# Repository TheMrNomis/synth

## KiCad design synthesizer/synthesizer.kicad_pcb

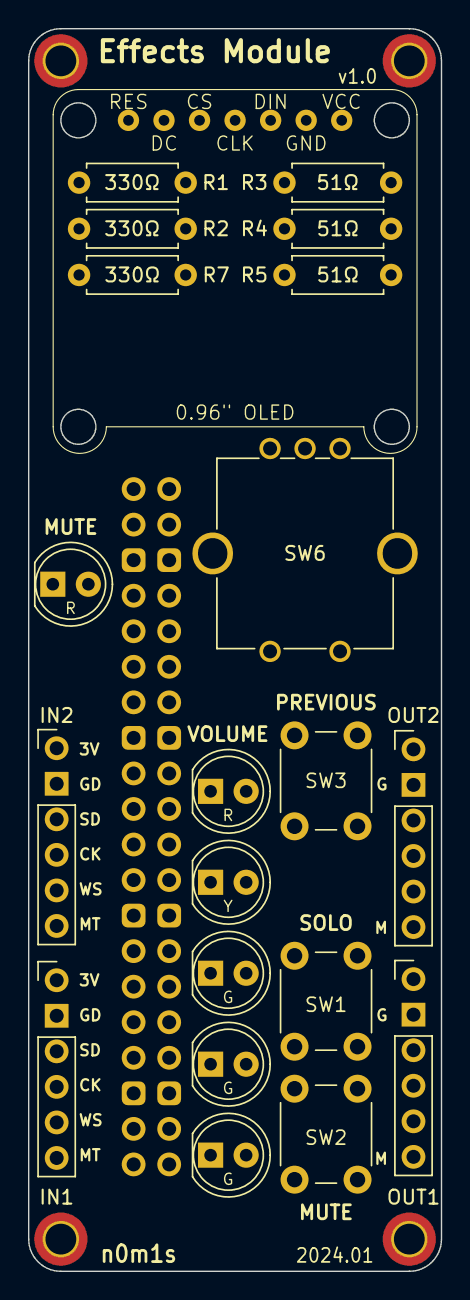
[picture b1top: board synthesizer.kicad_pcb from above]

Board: 2 copper layers, 29.5 x 88.8 mm, 26 parts (1 on the bottom side), 26 nets, no tracks yet.

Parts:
D2: RED; LED_D5.0mm
H1, H2, H3, H4: MountingHole_Pad; MountingHole_2.2mm_M2_DIN965_Pad_TopBottom
IN1, IN2: PannelConnector
OUT1, OUT2: PannelConnector
R1, R2, R7: 330Ω; R_Axial_DIN0207_L6.3mm_D2.5mm_P7.62mm_Horizontal
R3, R4, R5: 51Ω; R_Axial_DIN0207_L6.3mm_D2.5mm_P7.62mm_Horizontal
S1: 0.96inOLED
SW1: SW_SOLO; SW_PUSH_6mm_H5mm
SW2: SW_MUTE; SW_PUSH_6mm_H5mm
SW3: SW_PREV; SW_PUSH_6mm_H5mm
SW6: RotaryEncoder_Switch; RotaryEncoder_Bourns_Vertical_PEC12R-3xxxF-Sxxxx
U1: RaspberryPi_Pico; RPi_connector
VU1: RED; LED_D5.0mm
VU2: YELLOW; LED_D5.0mm
VU3, VU4, VU5: GREEN; LED_D5.0mm

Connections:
+3.3V: IN1.1 (VIN), IN2.1 (VIN), OUT1.1 (VIN), OUT2.1 (VIN), S1.7 (VCC), U1.36 (3V3)
/I2S_IN1_SCK: IN1.4 (SCK), U1.14 (GPIO10)
/I2S_IN1_SD: IN1.3 (SD), U1.12 (GPIO9)
/I2S_IN1_WS: IN1.5 (WS), U1.15 (GPIO11)
/I2S_IN2_SCK: IN2.4 (SCK), U1.10 (GPIO7)
/I2S_IN2_SD: IN2.3 (SD), U1.9 (GPIO6)
/I2S_IN2_WS: IN2.5 (WS), U1.11 (GPIO8)
/I2S_OUT_SCK: OUT1.4 (SCK), OUT2.4 (SCK), U1.19 (GPIO14)
/I2S_OUT_SD: OUT1.3 (SD), OUT2.3 (SD), U1.17 (GPIO13)
/I2S_OUT_WS: OUT1.5 (WS), OUT2.5 (WS), U1.20 (GPIO15)
/MUTE_BTN: SW2.2, U1.16 (GPIO12)
/MUTE_LED: D2.2 (A), U1.1 (GPIO0)
/MUTE_SIG: IN1.6 (MUTE), IN2.6 (MUTE), OUT1.6 (MUTE), OUT2.6 (MUTE), U1.29 (GPIO22)
/R7D2: D2.1 (K), R7.2
/SOLO_BTN: SW1.2, U1.27 (GPIO21)
/VU_GREEN1: U1.24 (GPIO18), VU3.2 (A)
/VU_GREEN2: U1.22 (GPIO17), VU4.2 (A)
/VU_GREEN3: U1.21 (GPIO16), VU5.2 (A)
/VU_R1: R1.2, VU1.1 (K)
/VU_R2: R2.2, VU2.1 (K)
/VU_R3: R3.2, VU3.1 (K)
/VU_R4: R4.2, VU4.1 (K)
/VU_R5: R5.2, VU5.1 (K)
/VU_RED: U1.26 (GPIO20), VU1.2 (A)
/VU_YELLOW: U1.25 (GPIO19), VU2.2 (A)
GND: H1.1, H2.1, H3.1, H4.1, IN1.2 (GND), IN2.2 (GND), OUT1.2 (GND), OUT2.2 (GND), R1.1, R2.1, R3.1, R4.1, R5.1, R7.1, S1.6 (GND), SW1.1, SW2.1, SW3.1, SW6.S2, U1.3 (GND), U1.8 (GND), U1.13 (GND), U1.18 (GND), U1.23 (GND), U1.28 (GND), U1.33 (AGND), U1.38 (GND)

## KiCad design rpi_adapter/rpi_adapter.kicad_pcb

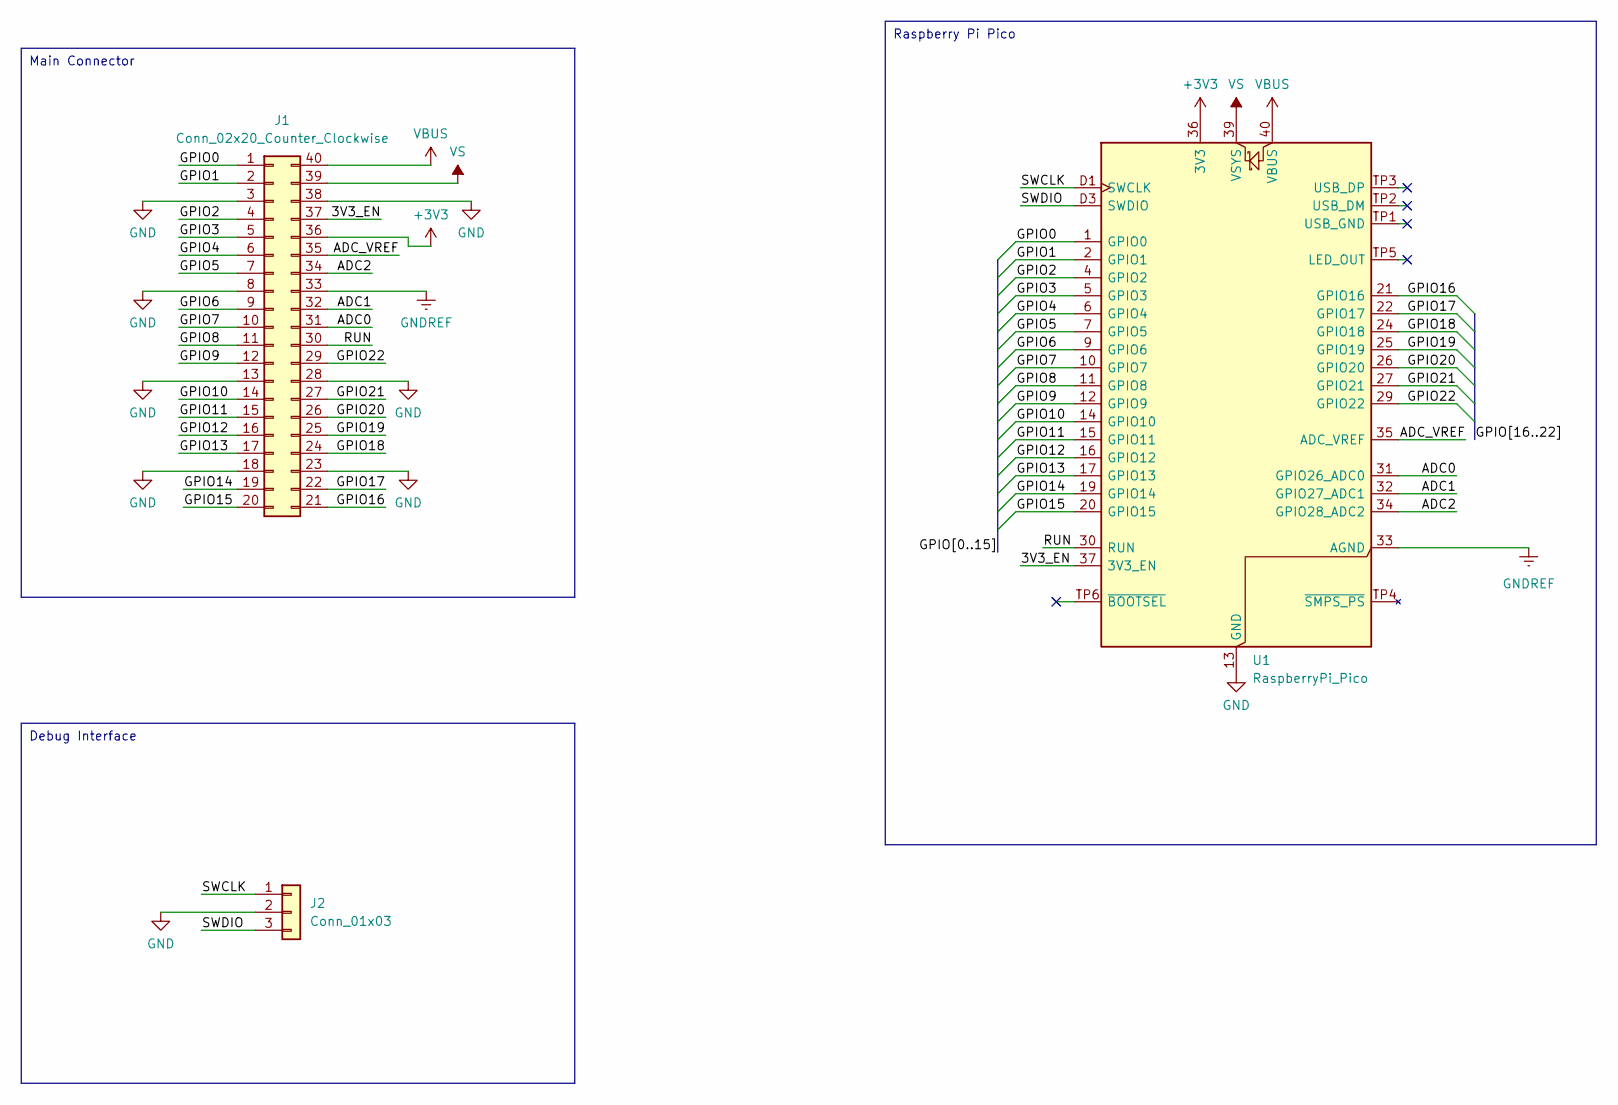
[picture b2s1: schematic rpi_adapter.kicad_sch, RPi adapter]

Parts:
J1: Conn_02x20_Counter_Clockwise; PinHeader_2x20_P2.54mm_Vertical
J2: Conn_01x03; JST_XH_B3B-XH-AM_1x03_P2.50mm_Vertical
U1: RaspberryPi_Pico; RaspberryPi_Pico_Original_SMD_MountingHoles_Castellated_Han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

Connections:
+3V3: J1.36, U1.36 (3V3)
/3V3_EN: J1.37, U1.37 (3V3_EN)
/ADC0: J1.31, U1.31 (GPIO26_ADC0)
/ADC1: J1.32, U1.32 (GPIO27_ADC1)
/ADC2: J1.34, U1.34 (GPIO28_ADC2)
/ADC_VREF: J1.35, U1.35 (ADC_VREF)
/GPIO0: J1.1, U1.1 (GPIO0)
/GPIO1: J1.2, U1.2 (GPIO1)
/GPIO2: J1.4, U1.4 (GPIO2)
/GPIO3: J1.5, U1.5 (GPIO3)
/GPIO4: J1.6, U1.6 (GPIO4)
/GPIO5: J1.7, U1.7 (GPIO5)
/GPIO6: J1.9, U1.9 (GPIO6)
/GPIO7: J1.10, U1.10 (GPIO7)
/GPIO8: J1.11, U1.11 (GPIO8)
/GPIO9: J1.12, U1.12 (GPIO9)
/GPIO10: J1.14, U1.14 (GPIO10)
/GPIO11: J1.15, U1.15 (GPIO11)
/GPIO12: J1.16, U1.16 (GPIO12)
/GPIO13: J1.17, U1.17 (GPIO13)
/GPIO14: J1.19, U1.19 (GPIO14)
/GPIO15: J1.20, U1.20 (GPIO15)
/GPIO16: J1.21, U1.21 (GPIO16)
/GPIO17: J1.22, U1.22 (GPIO17)
/GPIO18: J1.24, U1.24 (GPIO18)
/GPIO19: J1.25, U1.25 (GPIO19)
/GPIO20: J1.26, U1.26 (GPIO20)
/GPIO21: J1.27, U1.27 (GPIO21)
/GPIO22: J1.29, U1.29 (GPIO22)
/RUN: J1.30, U1.30 (RUN)
/SWCLK: J2.1, U1.D1 (SWCLK)
/SWDIO: J2.3, U1.D3 (SWDIO)
GND: J1.3, J1.8, J1.13, J1.18, J1.23, J1.28, J1.38, J2.2, U1.3 (GND), U1.8 (GND), U1.13 (GND), U1.18 (GND), U1.23 (GND), U1.28 (GND), U1.38 (GND), U1.D2 (GND)
GNDREF: J1.33, U1.33 (AGND)
VBUS: J1.40, U1.40 (VBUS)
VS: J1.39, U1.39 (VSYS)

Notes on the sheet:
Raspberry Pi Pico
Debug Interface
Main Connector

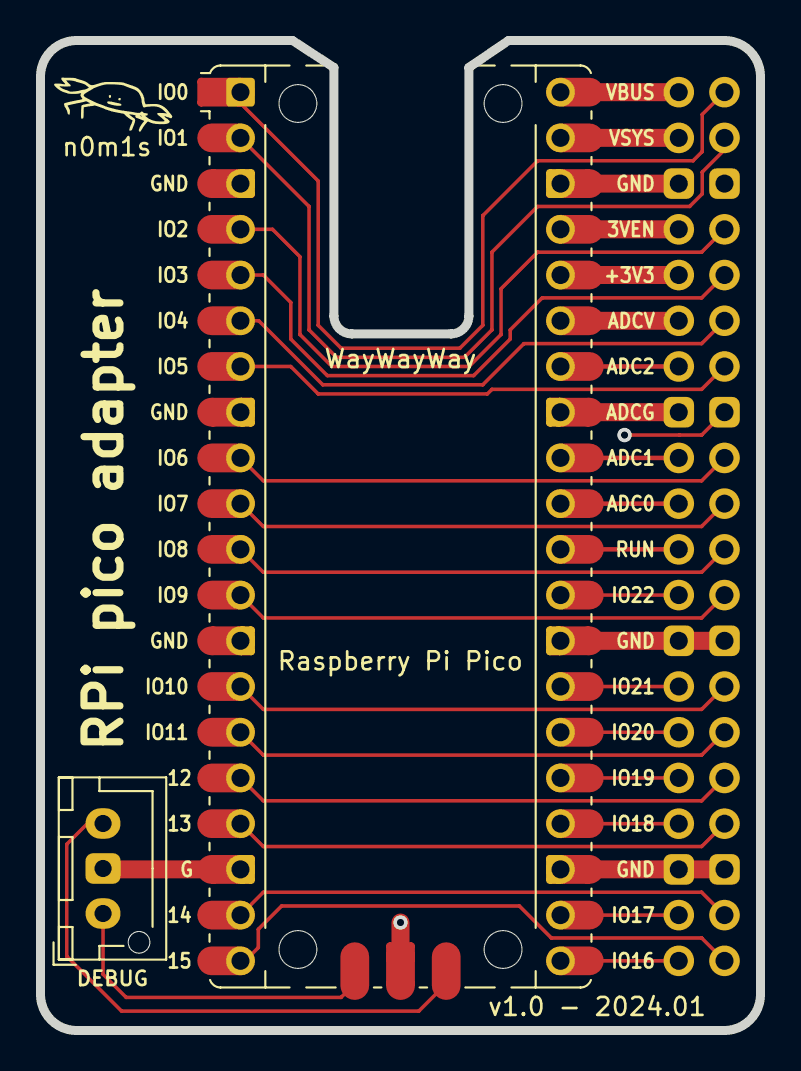
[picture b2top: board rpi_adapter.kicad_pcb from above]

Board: 2 copper layers, 40.0 x 55.0 mm, 3 parts (1 on the bottom side), 36 nets.

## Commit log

2024-01-10 Added pi pico library
2024-01-10 Finished PCB
2024-01-10 Fix DRC + output gerber files
2024-01-17 Updated schematics
